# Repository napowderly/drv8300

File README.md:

# DRV8300 | 100-V Three-Phase BLDC Gate Driver

The DRV8300 is a three-phase BLDC Gate Driver used to drive N-Channel MOSFET Half-Bridges using integrated bootstrap diodes.

Package: VQFN (24)

Key Specs:
- Integrated bootstrap diodes
- Cross conduction prevention
- 3V3 to 5V logic supported
- Supports independent high and low gate control.

Datasheet: https://www.ti.com/lit/ds/symlink/drv8300.pdf?ts=1711538531384

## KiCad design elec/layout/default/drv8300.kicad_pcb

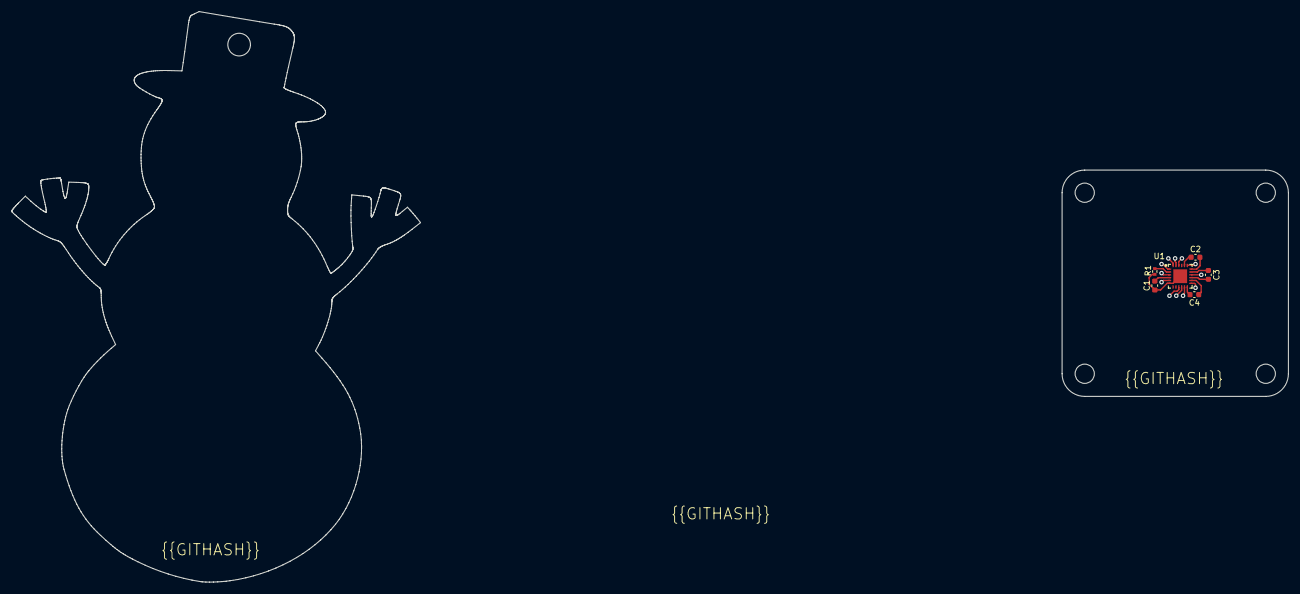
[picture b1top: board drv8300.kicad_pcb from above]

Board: 2 copper layers, 40.0 x 40.0 mm, 6 parts (0 on the bottom side), 9 nets.

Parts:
C1, C2, C3, C4: 50V 1uF X5R ±10% 0603 Multilayer Ceramic Capacito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; C0603
R1: 62.5mW Thick Film Resistors ±100ppm/℃ ±1% 40.2kΩ 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; R0402
U1: VQFN-24_L4.0-W4.0-P0.50-TL-EP2.5

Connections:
gnd: C1.2, R1.2, U1.6, U1.25
ic-vcc: C2.1, U1.20
ic-vcc-1: C3.1, U1.17
ic-vcc-2: C4.1, U1.14
vcc: C1.1, U1.4
vcc-3: R1.1, U1.2
vcc-14: C2.2, U1.18
vcc-15: C3.2, U1.15
vcc-16: C4.2, U1.12

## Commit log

2024-02-18 Configure project
2024-02-19 some progress
2024-02-19 initial build - has bugs
2024-02-20 that was gross, take two
2024-02-28 got it building
2024-02-28 fixed bootstrap typo
2024-03-28 connected bypass cap and ic ground
2024-03-28 added layout
2024-03-28 minor layout fix
2024-03-28 added a lot of layout
2024-03-28 added a lot of layout and fix
2024-03-28 added readme
